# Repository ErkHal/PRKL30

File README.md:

# PRKL30

## About
30% Custom mechanical keyboard designed  
for the Finnish Mechanical Keyboard Community

Designed by:  
- Ergorius (AKA [ErkHal](https://github.com/ErkHal))
- Tooni Skyy ([TooniSkyy on Github](https://github.com/TooniSkyy))
- Migiii
- Ortho-leaning

## Specs

- 30%, ultra-portable layout
- Powered by QMK Firmware -> [QMK repo folder](https://github.com/qmk/qmk_firmware/tree/master/keyboards/handwired/prkl30)
- Cherry MX, Alps and Choc switch support
- Works with a Pro Micro or Adafruit Feather for bluetooth
- Supports one rotary encoder

## Making it yourself

## PCB
"gerber" folder has the files needed for PCB orders, you can just send the ZIP file to the manufacturer of your choice.  

## Case & Plate
"KLE" folder has layout files that you can use to order plates and make KLE layout pictures for keymap readmes.  
You can use the kle_raw.txt data to create plate files with [ai03 plate generator](https://kbplate.ai03.me/) or [swillkb plate generator](http://builder.swillkb.com/)

There are a few different acrylic case designs [in this repo](https://github.com/TooniSkyy/prkl30-case)

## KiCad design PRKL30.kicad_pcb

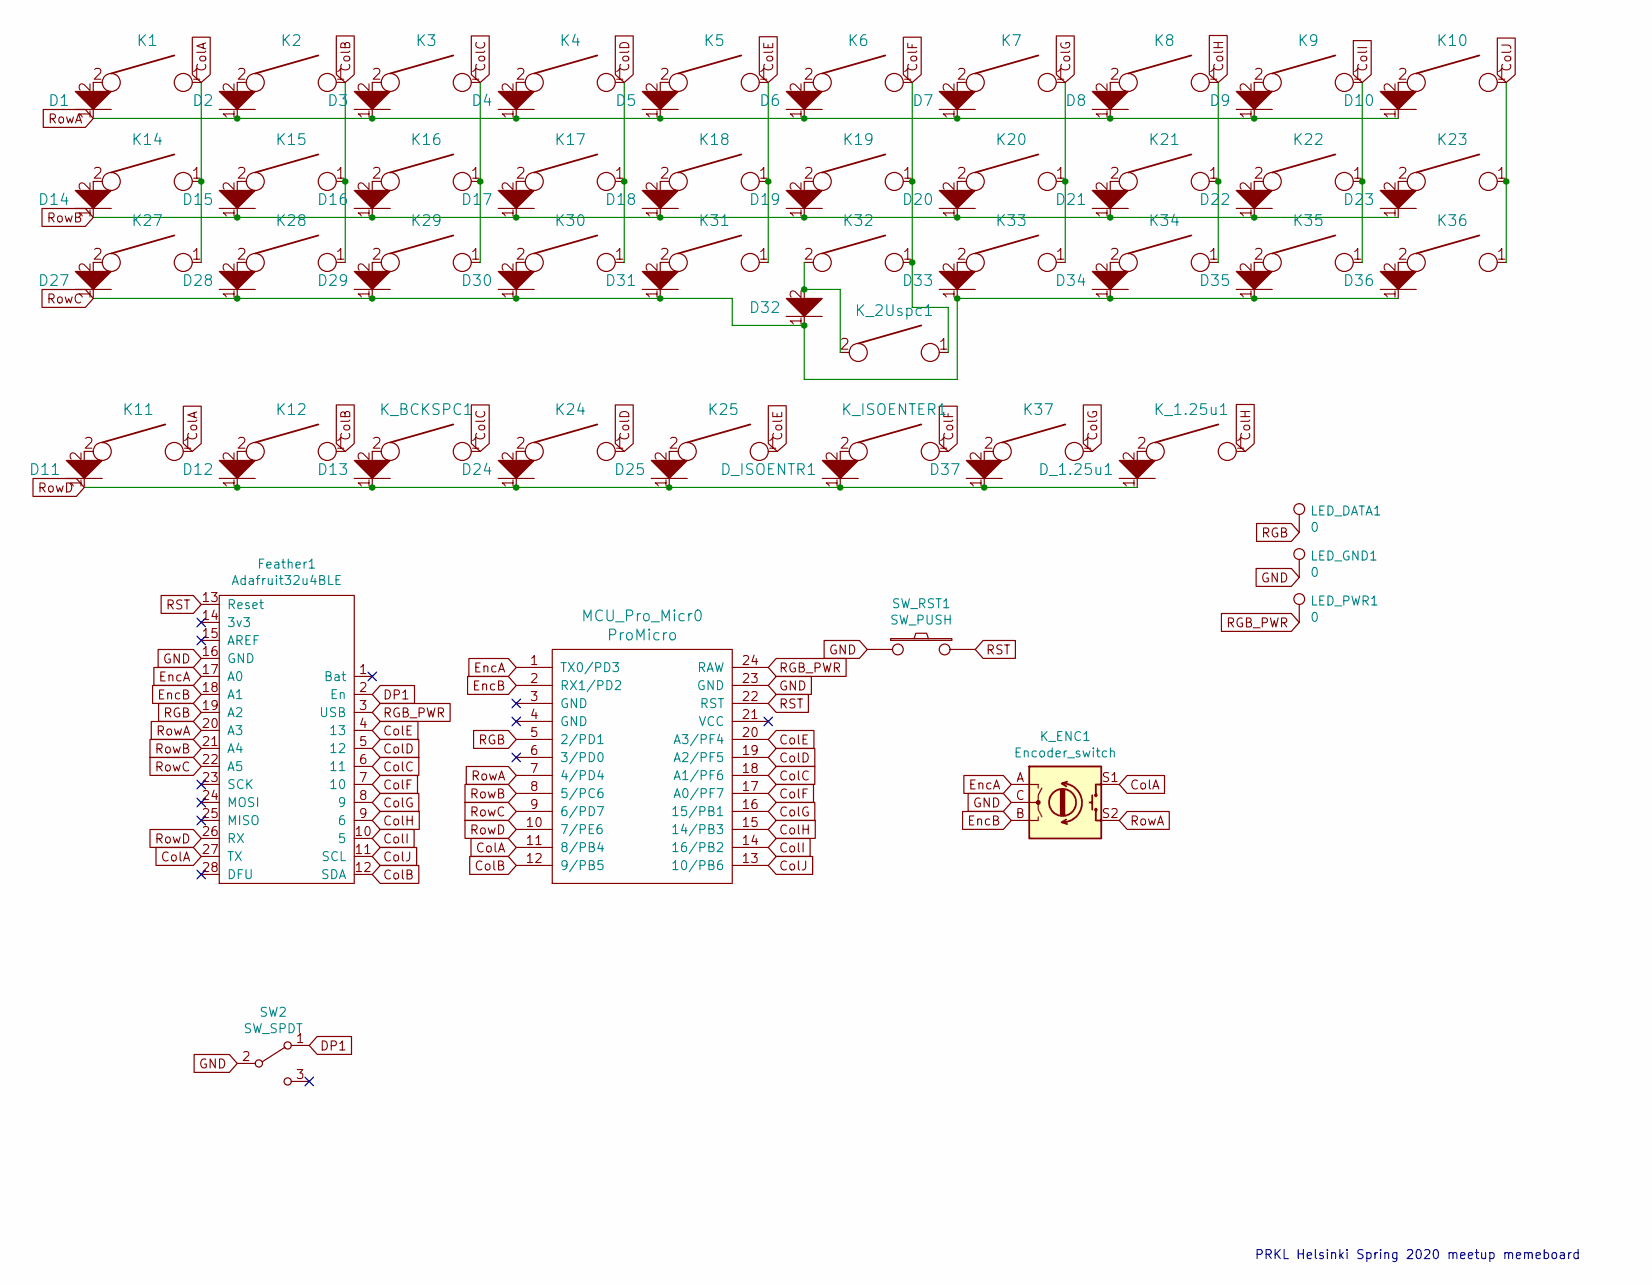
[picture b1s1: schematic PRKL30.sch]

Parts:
D1, D2, D3, D4, D5, D6, D7, D8, D9, D10, D11, D12, D13, D14, D15, D16, D17, D18, D19, D20, D21, D22, D23, D24, D25, D27, D28, D29, D30, D31, D32, D33, D34, D35, D36, D37: D; D_SOD123_axial
D_1.25u1: D; D_SOD123_axial
D_ISOENTR1: D; D_SOD123_axial
Feather1: Adafruit32u4BLE
K1, K2, K3, K4, K5, K6, K7, K8, K9, K10, K11, K12, K14, K15, K16, K17, K18, K19, K20, K21, K22, K23, K24, K25, K27, K28, K29, K30, K31, K32, K33, K34, K35, K36, K37: KEYSW; MX-Alps-Choc-1U-NoLED
K_1.25u1: KEYSW; MX-Alps-Choc-1U-NoLED
K_2Uspc1: KEYSW; MX-Alps-Choc-2U
K_BCKSPC1: KEYSW; MX-Alps-Choc-1U-NoLED
K_ENC1: Encoder_switch; RotaryEncoder_Alps_EC11E-Switch_Vertical_H20mm
K_ISOENTER1: KEYSW; MX-Alps-Choc-2U
LED_DATA1: 0; SinglePad
LED_GND1: 0; SinglePad
LED_PWR1: 0; SinglePad
MCU_Pro_Micr0: ProMicro; ArduinoProMicro-BackSide
SW2: SW_SPDT; SW_SPDT_PCM12
SW_RST1: SW_PUSH; SW_SPST_TL3342

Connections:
ColA: Feather1.27 (TX), K1.1, K11.1, K14.1, K27.1, K_ENC1.S1, MCU_Pro_Micr0.11 (8/PB4)
ColB: Feather1.12 (SDA), K2.1, K12.1, K15.1, K28.1, MCU_Pro_Micr0.12 (9/PB5)
ColC: Feather1.6 (11), K3.1, K16.1, K29.1, K_BCKSPC1.1, MCU_Pro_Micr0.18 (A1/PF6)
ColD: Feather1.5 (12), K4.1, K17.1, K24.1, K30.1, MCU_Pro_Micr0.19 (A2/PF5)
ColE: Feather1.4 (13), K5.1, K18.1, K25.1, K31.1, MCU_Pro_Micr0.20 (A3/PF4)
ColF: Feather1.7 (10), K6.1, K19.1, K32.1, K_2Uspc1.1, K_ISOENTER1.1, MCU_Pro_Micr0.17 (A0/PF7)
ColG: Feather1.8 (9), K7.1, K20.1, K33.1, K37.1, MCU_Pro_Micr0.16 (15/PB1)
ColH: Feather1.9 (6), K8.1, K21.1, K34.1, K_1.25u1.1, MCU_Pro_Micr0.15 (14/PB3)
ColI: Feather1.10 (5), K9.1, K22.1, K35.1, MCU_Pro_Micr0.14 (16/PB2)
ColJ: Feather1.11 (SCL), K10.1, K23.1, K36.1, MCU_Pro_Micr0.13 (10/PB6)
DP1: Feather1.2 (En), SW2.1 (A)
EncA: Feather1.17 (A0), K_ENC1.A, MCU_Pro_Micr0.1 (TX0/PD3)
EncB: Feather1.18 (A1), K_ENC1.B, MCU_Pro_Micr0.2 (RX1/PD2)
GND: Feather1.16 (GND), K_ENC1.C, LED_GND1.1, MCU_Pro_Micr0.23 (GND), SW2.2 (B), SW_RST1.1
unnamed: D1.2, K1.2
unnamed: D2.2, K2.2
unnamed: D3.2, K3.2
unnamed: D4.2, K4.2
unnamed: D5.2, K5.2
unnamed: D6.2, K6.2
unnamed: D7.2, K7.2
unnamed: D8.2, K8.2
unnamed: D9.2, K9.2
unnamed: D10.2, K10.2
unnamed: D11.2, K11.2
unnamed: D12.2, K12.2
unnamed: D13.2, K_BCKSPC1.2
unnamed: D14.2, K14.2
unnamed: D15.2, K15.2
unnamed: D16.2, K16.2
unnamed: D17.2, K17.2
unnamed: D18.2, K18.2
unnamed: D19.2, K19.2
unnamed: D20.2, K20.2
unnamed: D21.2, K21.2
unnamed: D22.2, K22.2
unnamed: D23.2, K23.2
unnamed: D24.2, K24.2
unnamed: D25.2, K25.2
unnamed: D27.2, K27.2
unnamed: D28.2, K28.2
unnamed: D29.2, K29.2
unnamed: D30.2, K30.2
unnamed: D31.2, K31.2
unnamed: D32.2, K32.2, K_2Uspc1.2
unnamed: D33.2, K33.2
unnamed: D34.2, K34.2
unnamed: D35.2, K35.2
unnamed: D36.2, K36.2
unnamed: D37.2, K37.2
unnamed: D_1.25u1.2, K_1.25u1.2
unnamed: D_ISOENTR1.2, K_ISOENTER1.2
RGB: Feather1.19 (A2), LED_DATA1.1, MCU_Pro_Micr0.5 (2/PD1)
RGB_PWR: Feather1.3 (USB), LED_PWR1.1, MCU_Pro_Micr0.24 (RAW)
RST: Feather1.13 (Reset), MCU_Pro_Micr0.22 (RST), SW_RST1.2
RowA: D1.1, D2.1, D3.1, D4.1, D5.1, D6.1, D7.1, D8.1, D9.1, D10.1, Feather1.20 (A3), K_ENC1.S2, MCU_Pro_Micr0.7 (4/PD4)
RowB: D14.1, D15.1, D16.1, D17.1, D18.1, D19.1, D20.1, D21.1, D22.1, D23.1, Feather1.21 (A4), MCU_Pro_Micr0.8 (5/PC6)
RowC: D27.1, D28.1, D29.1, D30.1, D31.1, D32.1, D33.1, D34.1, D35.1, D36.1, Feather1.22 (A5), MCU_Pro_Micr0.9 (6/PD7)
RowD: D11.1, D12.1, D13.1, D24.1, D25.1, D37.1, D_1.25u1.1, D_ISOENTR1.1, Feather1.26 (RX), MCU_Pro_Micr0.10 (7/PE6)

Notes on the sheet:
PRKL Helsinki Spring 2020 meetup memeboard

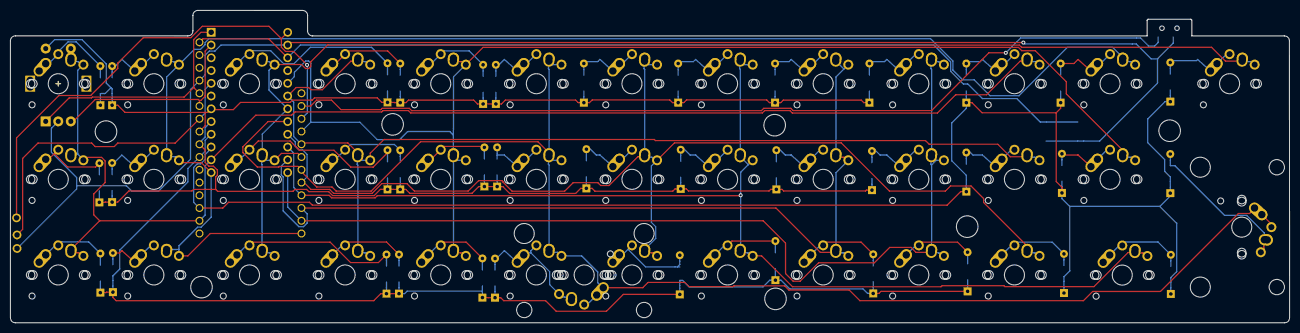
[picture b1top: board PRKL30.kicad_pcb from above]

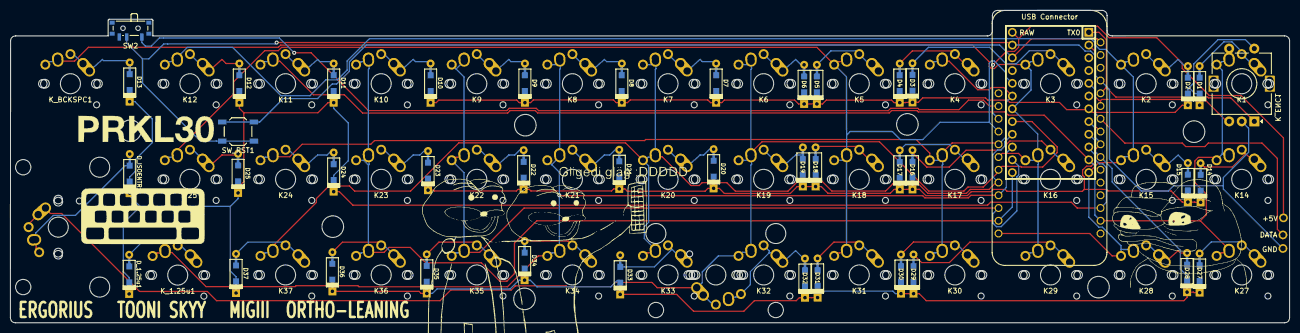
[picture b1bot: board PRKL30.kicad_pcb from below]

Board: 2 copper layers, 254.9 x 62.2 mm, 93 parts (44 on the bottom side), 59 nets.

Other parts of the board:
G_silk_gfx: LOGO_GFX; PRKL30SILK
M2_1, M2_2, M2_3, M2_4, M2_5, M2_6, M2_7: VAL**; spacer_m2

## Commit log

2020-01-04 Create LICENSE
2020-01-04 Add unfinished pcb
2020-01-05 Add WS2812B LED Strip support
2020-01-05 Move WS2812 pins to the side, rearrange diode footprints
2020-01-07 Change project name, clean up older files
2020-01-07 Add files via upload
    "valmiit kuvat ja silkit" kansiosta löytyy png ja silkit. Jostain syystä en saannut renderissä näkymään silkkejä vaikka ne näkyvät pcb view.
2020-01-08 Add files via upload
    Silkit aseteltu
2020-01-08 Prototype version
2020-01-28 Rotate one diode footprint, Add silkscreen text for underglow pins, fix autoroute mistakes
2020-01-28 Cleanup old files, generate new gerbers
2020-01-28 edited and flipped mc positions, edited silks also moved diodes and reset button
2020-01-29 mc's flipped, pro micro moved, silks fixed, reset button and diodes moved
2020-01-29 Move bluetooth switch, make room for battery between middle standoffs
2020-02-03 Add new routings, change mounting holes to M2
2020-02-03 Generated new plot and drill files
2020-02-06 Add README
2020-02-10 moved ble switch and edited pcb outlines and traces related to that
2020-03-10 Add KLE files, update documentation
2020-10-06 Create LICENSE
    Add MIT license.
2021-05-01 Push rev 1.1 with bigger mount holes to allow for M2 spacers
2022-02-22 Push graphics and gerbers of V1.1
2022-02-22 Push build guide
2023-11-01 Update README.md
    Typo correction and format cleaning
